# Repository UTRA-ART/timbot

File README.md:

# Timbot

A ROS2-based autonomous robot developed by UTRA-ART.

## Overview

Timbot is a robotics platform featuring computer vision, odometry, navigation, and motor control capabilities. The project is organized into modular ROS2 packages for easy development and maintenance.

## Getting Started

### WSL Setup

If you're using Windows Subsystem for Linux (WSL), please refer to the **setup.pdf** file in this repository for detailed instructions on setting up your WSL environment for ROS2 development.

### Contributing

Before contributing to this project, please read the **[CONTRIBUTING.md](CONTRIBUTING.md)** file. It contains essential information about:

- Setting up ROS2 packages in the workspace
- Creating new packages in directories like `odom`, `cv`, `nav`, etc.
- Building and testing your code
- Branching practices and workflow
- Pull request guidelines

## Project Structure

```
timbot/
├── cv/              # Computer vision packages
├── odom/            # Odometry packages
├── nav/             # Navigation packages
├── sensor-drivers/  # Sensor driver packages
├── motor-control/   # Motor control packages
├── embedded/        # Embedded system packages
├── rpi/             # Raspberry Pi specific packages
├── gazebo-worlds/   # Simulation world files
└── description/     # Robot description (URDF/xacro)
```

## Quick Start

1. Follow the WSL setup instructions in `setup.pdf` (if applicable)
2. Read the [CONTRIBUTING.md](CONTRIBUTING.md) file for development setup
3. Install ROS2 dependencies
4. Build the workspace with `colcon build`
5. Start developing!

## License

See [LICENSE](LICENSE) file for details.

## Contact

For questions or issues, please open an issue on GitHub or contact the UTRA-ART team.

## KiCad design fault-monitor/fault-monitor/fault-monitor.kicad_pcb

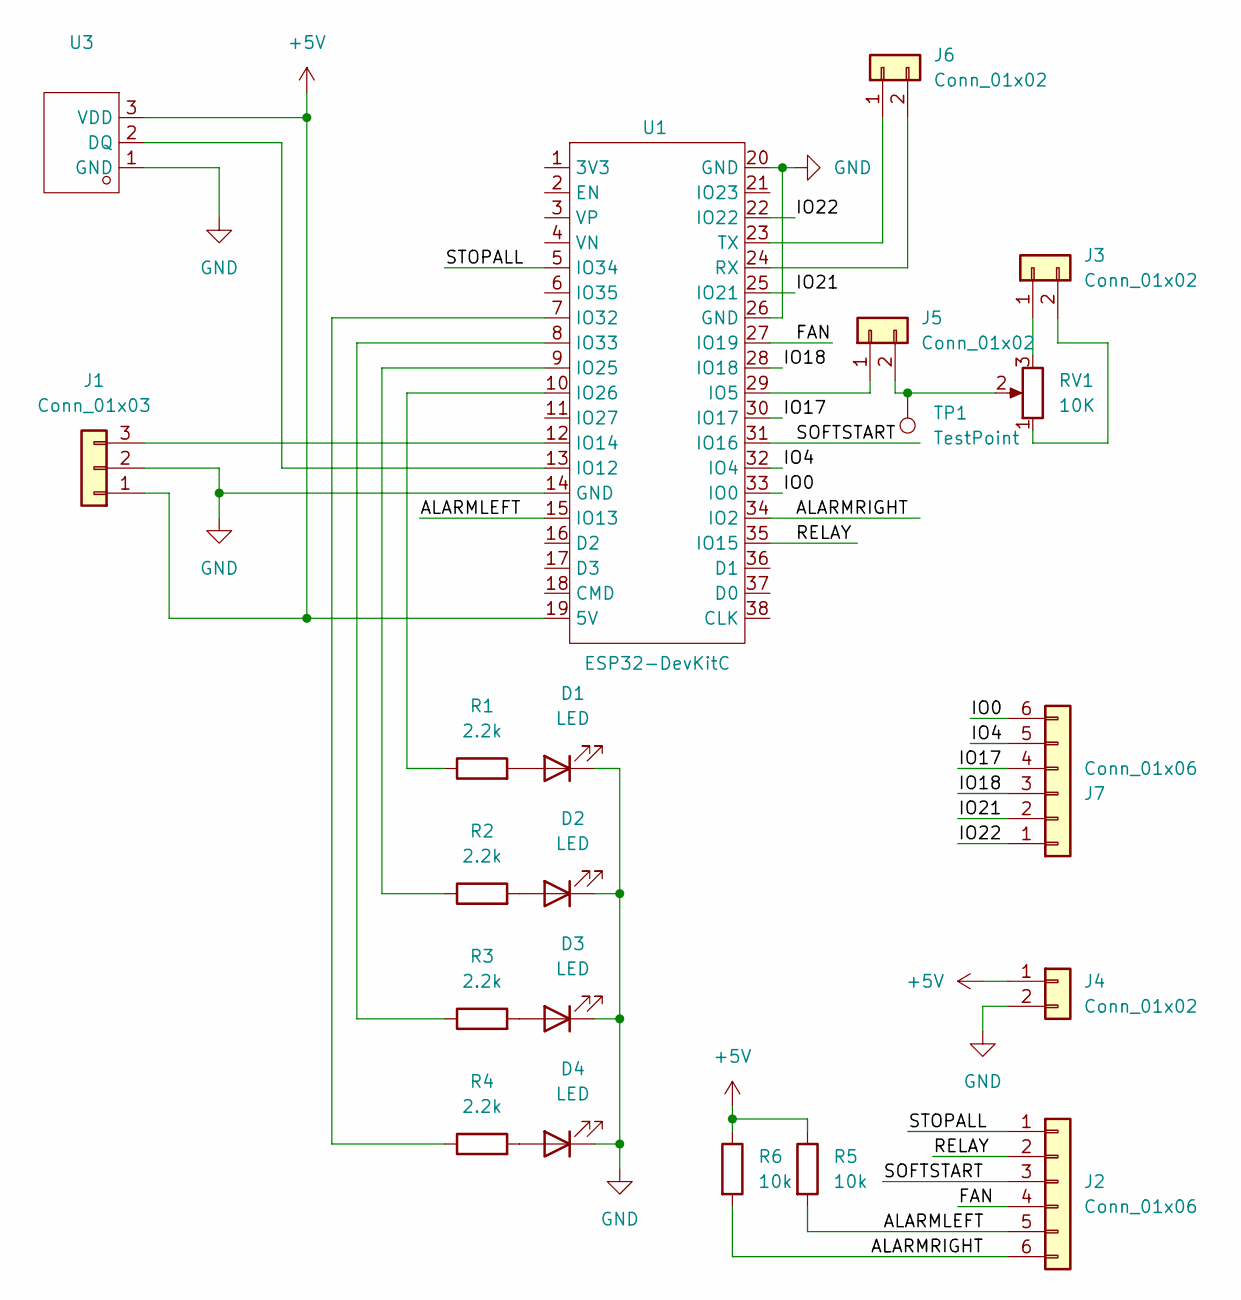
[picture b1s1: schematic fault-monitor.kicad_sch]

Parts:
D1, D2, D3, D4: LED; LED_D5.0mm
J1: Conn_01x03; TerminalBlock_MaiXu_MX126-5.0-03P_1x03_P5.00mm
J2, J7: Conn_01x06; TerminalBlock_MaiXu_MX126-5.0-06P_1x06_P5.00mm
J3, J4, J6: Conn_01x02; TerminalBlock_MaiXu_MX126-5.0-02P_1x02_P5.00mm
J5: Conn_01x02; PinHeader_1x02_P2.54mm_Vertical
R1, R2, R3, R4: 2.2k; R_Axial_DIN0207_L6.3mm_D2.5mm_P10.16mm_Horizontal
R5, R6: 10k; R_Axial_DIN0207_L6.3mm_D2.5mm_P10.16mm_Horizontal
RV1: 10K; POT_N6L30T0N_AMP
TP1: TestPoint; PinHeader_1x01_P2.54mm_Vertical
U1: ESP32-DevKitC; ESP32-DevKitC-ReversePinOrder; Manufacturer Part ESP32-DevKitC; LCSC Part Name 开发板
U3: TO-92L; Manufacturer Part DS18B20T(XBLW); LCSC Part Name DS18B20T(XBLW)

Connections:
+5V: J1.1, J4.1, R5.1, R6.1, U1.19 (5V), U3.3 (VDD)
/ALARMLEFT: J2.5, R5.2, U1.15 (IO13)
/ALARMRIGHT: J2.6, R6.2, U1.34 (IO2)
/FAN: J2.4, U1.27 (IO19)
/IO0: J7.6, U1.33 (IO0)
/IO4: J7.5, U1.32 (IO4)
/IO17: J7.4, U1.30 (IO17)
/IO18: J7.3, U1.28 (IO18)
/IO21: J7.2, U1.25 (IO21)
/IO22: J7.1, U1.22 (IO22)
/RELAY: J2.2, U1.35 (IO15)
/SOFTSTART: J2.3, U1.31 (IO16)
/STOPALL: J2.1, U1.5 (IO34)
GND: D1.1 (K), D2.1 (K), D3.1 (K), D4.1 (K), J1.2, J4.2, U1.14 (GND), U1.20 (GND), U1.26 (GND), U3.1 (GND)
unnamed: D1.2 (A), R1.2
unnamed: D2.2 (A), R2.2
unnamed: D3.2 (A), R3.2
unnamed: D4.2 (A), R4.2
unnamed: J1.3, U1.12 (IO14)
unnamed: J3.1, RV1.3
unnamed: J3.2, RV1.1
unnamed: J5.1, U1.29 (IO5)
unnamed: J5.2, RV1.2, TP1.1
unnamed: J6.1, U1.23 (TX)
unnamed: J6.2, U1.24 (RX)
unnamed: U1.13 (IO12), U3.2 (DQ)
unnamed: R2.1, U1.9 (IO25)
unnamed: R1.1, U1.10 (IO26)
unnamed: R4.1, U1.7 (IO32)
unnamed: R3.1, U1.8 (IO33)

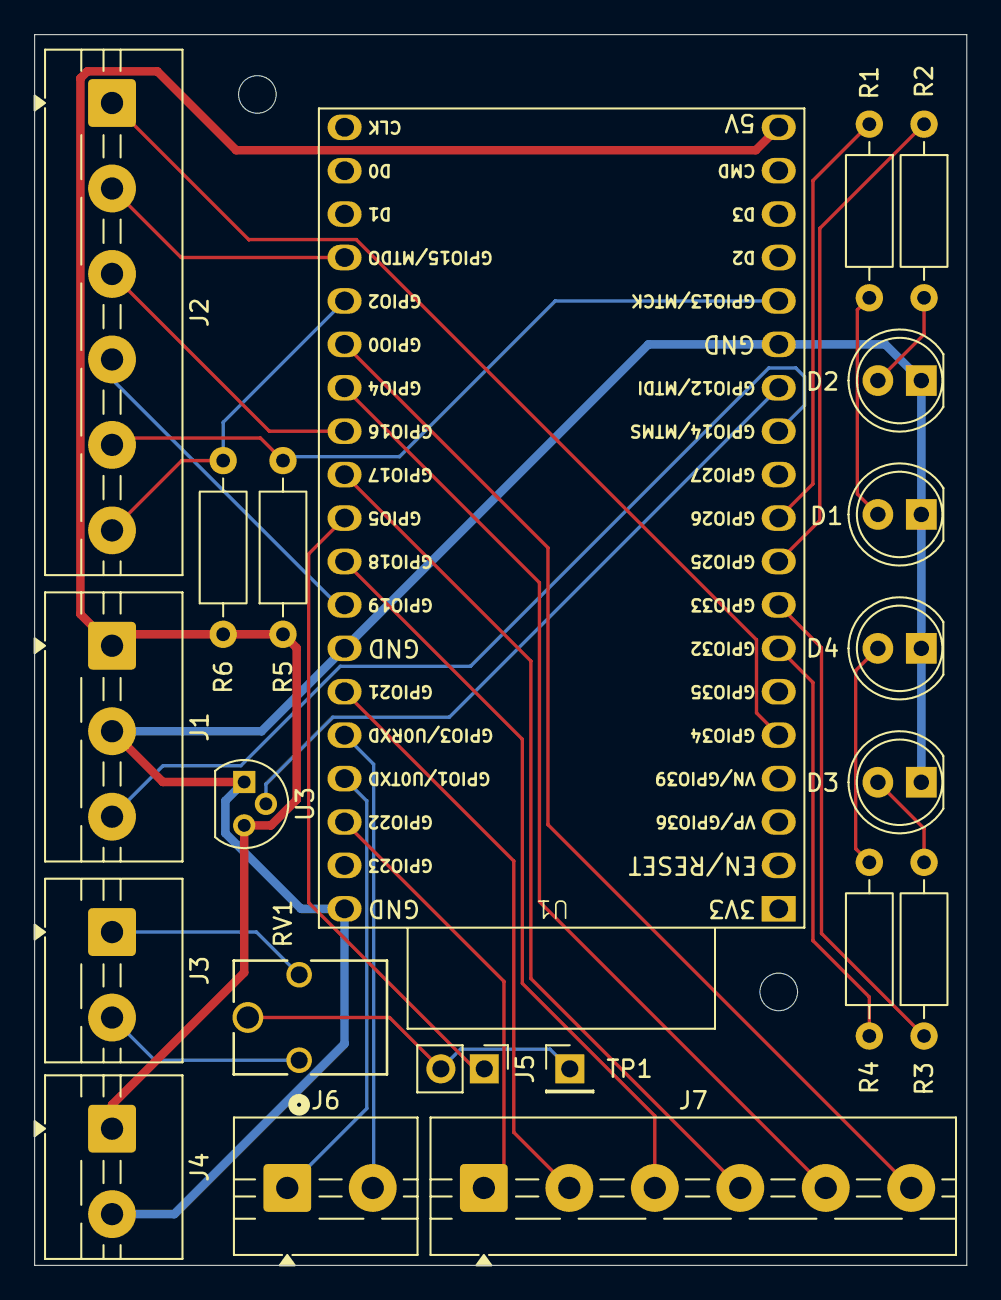
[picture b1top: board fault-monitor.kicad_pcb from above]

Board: 2 copper layers, 54.5 x 72.0 mm, 21 parts (0 on the bottom side), 30 nets.

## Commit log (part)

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2026-02-19 updating params
2026-02-27 updating the repo for being branched
2026-02-27 Adding ROS GUI
2026-02-27 added + tested the correct twist_mux package
2026-02-27 making the singular launch file
2026-02-28 common launch file created
2026-02-28 fixed typo in nav_options to properly connect callbacks
2026-02-28 ported motor_control.py to ros2
2026-02-28 Initial commit for setup
2026-02-28 ported odom_pub
2026-02-28 adding resources
2026-02-28 fixed readme
2026-02-28 fixed build issues with timbot gui
2026-02-28 added csv files and read data to array
2026-02-28 Add test visualization function and fixed import issues
2026-02-28 fixing submodules
2026-03-03 Add conversion from latitude, longitude and altitude to ENU coordinates
2026-03-05 Add data plotting function still WIP
2026-03-06 Add color coding representing time change
2026-03-07 Migrated odom_pub2
2026-03-07 Migrated read_odom_arduino.py
2026-03-07 Migrated sensors_arduino
2026-03-07 Added shutdown
2026-03-07 Pasted over docstring
2026-03-07 Added wrapper function for visualization and upscaled z-axis
2026-03-07 Fixed duplicate bagwriter, remvoed unused features
2026-03-07 Fixed Bagwriter issues
2026-03-07 Rename UTRA.zip to UTRA_ROVERSCHEMATIC.zip
    Schematic for ROVER
2026-03-07 add fault monitor code
2026-03-07 testing
2026-03-07 Added correct rover starting waypoints
2026-03-07 fixed the gps diverging issue
2026-03-09 faultmon readme
2026-03-13 added cv support in sim
2026-03-14 Add 2D visualization for rover path and altitude profile (WIP)
2026-03-17 update volt sensor pin
2026-03-19 updating some launch configurations
2026-03-19 fixing cmake
2026-03-21 Allowed for passing datum ad magnetic declination in sim.yaml.
    Added new working waypoints.
    Added new yaml files for nav2, where nav_params has had incorrect parameters removed, and nav_rpp navigates the map without collision, by using new RPP local controller and smac global planner.
2026-03-21 trying to fix the submodule setup
2026-03-21 removed help button
2026-03-21 Add initial implementation of Rover Path visualization tool with HTML, CSS, and JavaScript files
2026-03-21 added testing scripts
2026-03-21 /ramp_seg type fix
2026-03-21 added sensor submodules
2026-03-21 topic consistency hopefully fixed
2026-03-21 fixed submodules
2026-03-26 fixing the submodules
2026-03-26 updating a few params
2026-03-26 Fix camera in sim
2026-03-27 Add new weights for cv model
2026-03-27 Update nav2 to use lane detection cloud
2026-03-28 Added covariance LLA to ENU and shaded region to graphs
2026-03-28 Fixed nav file to work with CV, and added variable inflation radius per sensor. Added wait for datum, datum, and magnetic declination radius params to the sim.yaml
2026-03-28 Fixed errors and typos in the nav2_rpp
2026-03-28 implemented imu vis
2026-03-28 added covar calculations
2026-03-30 Change rviz for easier CV debugging
2026-04-02 Fix obstacle height ranges
2026-04-02 Use camera width/height for lane detection
2026-04-02 added empty world + world with ramp right in front of rover
2026-04-03 Refactor classical lane for future improvements
2026-04-03 Refactor mask application
2026-04-03 Refactor lane detection class
2026-04-03 Try new thresholding settings
2026-04-04 Add basic morphological filtering
2026-04-04 Link parameters to sim.yaml file
2026-04-04 Artificially set cv camera width/height to sim file width/height?
2026-04-04 Finally sync cv camera dimensions with cv pipeline
2026-04-04 Trial area based filter
2026-04-04 reverted nav2_rpp back to working order.
2026-04-04 Separate ML model into its own class, similar to classical
2026-04-04 Add comparison script for videos
2026-04-04 Add camera video exporter script
2026-04-04 Improve cv model comparison demonstration
2026-04-04 Fix shebang issue
2026-04-04 teleop twist keyboard fix
2026-04-04 added timbot gui bug fixes
2026-04-04 fixed ramp alignment
2026-04-04 Fix RVIZ not displaying
2026-04-04 Added gui bug fixes
2026-04-04 merged with main
2026-04-04 added lanes to ramp
2026-04-04 reverted odom changes
2026-04-04 updated old ramp
2026-04-04 made lane lines white
2026-04-04 added walls tp ramps
2026-04-04 updated ramp
2026-04-07 Increased height of ramp walls
2026-04-07 added map with no walls for testing CV
2026-04-17 Enable cv pipeline in sim config
2026-04-20 adding the sensor launches to the launch files
2026-04-20 Add standalone depth-to-pointcloud node
2026-04-20 Add height filtering to depth point cloud
2026-04-21 updating the lidar usb points
2026-04-21 changing odom pub to python
2026-04-21 updated ramp geometry
2026-04-21 Add ROI filtering to depth point cloud
2026-04-21 Publish obstacle point cloud topic
2026-04-21 Voxel downsample obstacle point cloud
2026-04-21 adding a arduino file
2026-04-21 test push
2026-04-21 Cluster obstacle point cloud
2026-04-21 Compute obstacle cluster metadata
2026-04-21 Publish ramp point cloud
2026-04-21 temp work
2026-04-22 fixing motor_control
2026-04-22 motorcontrol hotfixes
2026-04-22 changed readline to read in motor_control
2026-04-22 twist_mux/cmd_vel is just cmd_vel now
2026-04-22 Detect ramps with elevation grid
2026-04-22 Remove cluster ramp fallback
2026-04-22 trying to fix motor feedback
2026-04-22 working teleop, debugging feedback
2026-04-22 update teleop
2026-04-22 added patch to build on main laptop
2026-04-23 comment out ramp seg callback so that it doesn't gen ramp waypoints
2026-04-23 Fix floating construction barrels
2026-04-24 all sensors integrated except zed camera
2026-04-24 adding the script for the motor_control
2026-04-24 fixing the rpi connection issues
2026-04-25 updating camera and adding relay to depth map
2026-04-27 adding more debugging methods
2026-04-28 adding the open source zed driver
2026-04-28 working depth map
2026-04-28 tuning wheel odom
2026-05-02 Make lane detections persist
2026-05-02 Extend detection of left lane further
2026-05-04 Add camera exposure caliberation override
2026-05-04 Update comments
2026-05-04 Add gamma parameter to zed camera
2026-05-04 we will check this soon
2026-05-05 good software pracice
2026-05-05 Fix typo
2026-05-05 Fixed nav2_rpp.yaml file to correct limits for the lane detection and lidar for the costmap. Merged zed-calibration and fixed any errors with that branch. Added refresh_motor to automatically execute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
2026-05-08 Add odom, lane detections, obstacles to cartographer
2026-05-08 Add ZED pointcloud filtering pipeline
2026-05-09 feat: add rviz point cloud filter node and update display config
2026-05-09 build: add cmake config and update package.xml for pointcloud filter node
2026-05-09 feat: add three filtered point cloud displays to rviz config
2026-05-09 refactor: prefix new point cloud displays with ZED for clarity
2026-05-09 fix: use points_rviz frame as source of truth for filter node
    - Remove optical_to_base transform from filter node (input already in left_camera_link)
    - Filter directly on relay coordinates (left_camera_link frame convention)
    - Add pointcloud_rviz_filter node to robot_bringup.launch.py with absolute executable path
    - Fix executable permissions on filter script
    The filter now accepts points labeled as left_camera_link from the relay and applies ROI/height filtering without frame conversion.
2026-05-09 fix: apply min_height to ramp candidates in new filter node
    New filter ramp candidates now use same bounds as filtered points (min_height: 0.05m, max_height: 2.0m) instead of undefined ramp_grid params. This matches the new filter's coordinate system (left_ca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
2026-05-09 Restore ramp height filtering defaults
2026-05-09 Add distance-based point cloud height filtering
2026-05-10 Fixed bugs in motor_odom so that it works fully now (hopefully), added controlling with the ps4, fixed bugs with teleop, added new nav2 file based on the espresso configuration, added new cmd_vel_sub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
2026-05-10 got imu to work, turns out it was battery issue
2026-05-10 developed new odom pathway. Still need to test with wheel encoders, and test with the gps to see cartographer performance. Changed wheel encoder topic to wheel_odom
2026-05-12 ekf_local now is accurate to translations and rotations. This was fixed by changing the wheel_odom message frame header id to odom. Changed imu in local ekf to only output angular vel. Cartographer s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
2026-05-14 Fix ZED camera ROS parameter adjustment
2026-05-20 Adjusted cartographer weights to trust incoming odometry more than local slam odometry. Changed the inflation radius of nav2_rpp to be smaller around the object.
2026-05-20 Added critics to nav2 file, added navigate to gps service in navigation, readded gps into timbot.launch, further tuning of the camera.
2026-05-22 nav2 tuning - working pretty well with this config
2026-05-22 inc inflation_radius to get rid of error
2026-05-25 Fixed nav issues using new nav file that is very similar to last years movebase yaml file.
2026-05-27 Add ZED camera denoising parameters
2026-05-27 Fix comment
2026-05-28 fix gps heading by using datum
2026-05-28 fixed nav2 and gps on this so that we have less issues with the rover fidgeting around when reaching an obstacle by increasing the inflation radius and decreasing cost factor for the global costmap, 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
2026-05-29 updated STL files, still broken bc of some filenames
2026-05-29 fixed filenames of wheels and lidars
2026-05-29 put the tright declination radians
2026-05-29 reorganizing cv modules + switching ramp_seg to be done by depth_detection
2026-05-29 add cv lane + obstacle detections to nav2
2026-05-29 cleanup
2026-05-29 competition GPS waypoints
2026-05-29 change to clockwise
2026-05-29 oisjgv
2026-05-29 filename fix #2
2026-05-29 rm depth camera obstacles plugins for now
2026-05-29 instead of removing plugins, just disabled the cv obstacle detection for now
2026-05-29 made odom_sim.yaml to odom.yaml
2026-05-29 fixed changes with the gazebo sim, and got launch to run
2026-05-29 imu position patch
2026-05-29 display launch patch to remove refs to espresso
2026-05-29 48utksd
2026-05-29 finally fucking did it
2026-05-30 small bug fix for moving the cv modules
2026-05-30 setting up the ENU for magnometer
2026-05-30 gps yaw fix
2026-05-30 reverting the direction
2026-05-30 claude work
2026-05-30 relay bug
2026-05-30 fixed sign error in URDF
2026-05-30 relay workoing, need to test for the offset parameter tuning.
2026-05-30 relay to test imu
2026-05-30 working gps in enu frame
2026-05-30 adding the patch to the build script
2026-05-31 working imu
2026-05-31 "No more nab relay"
2026-05-31 some errors from the nav_relay from syntax, as well as including it in the cmake_list
2026-05-31 making odom testing script
2026-05-31 updated to test cart output
2026-05-31 trying to setup cart somehow - doesn't really work right now tho
2026-05-31 some tuning attempt but rotation is still bad
2026-05-31 changes to architecture - to be tested
2026-05-31 fixed errors with the nav2 relay (hopefully, need to test). Added the teleop_key to the timbot launch file as well as to the config file. NEED TO TEST.
2026-06-01 working relay + working nav node + fixed zed tf
2026-06-01 fixing the depth pointcloud relay
2026-06-01 Added obstacle + inflation layers from cv
2026-06-01 running gps point
2026-06-01 map = odom TF
2026-06-01 disable publishing of cartographer TF
2026-06-01 comment out global EKF
2026-06-01 change nav2 navigator to use local odom and rm global ekf from navigate_waypoints
2026-06-01 implemented using octomap without cartographer for mapping. created static identity transform for odom to map, created point mergeing for the lidar and the camera, added the octomap nodes and server 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
2026-06-01 working chudmobile
2026-06-01 fixed chud mobile
2026-06-01 use imu yaw & yaw angular vel relatively
2026-06-01 launch the auto_nav_relay on comp instead of load_waypoints
2026-06-01 rtab for visual odom + relay fix
2026-06-01 somewhat working visual odom - but still lots of drift in location
2026-06-01 small fixes
2026-06-01 i don't rmb
2026-06-01 added velocity smoother into the nav2 params file and launch file, to heopefullt smooth velocity commands from the controller. now controller remapped to ctrl_vel, which is sent to velocity smoother 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
